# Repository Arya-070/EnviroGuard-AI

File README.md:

# 🚀 EnviroGuard-AI
### *A Smart, Modular Infrastructure Monitoring System Powered by Edge AI and ESP32-S3*

---

## 🌍 Overview
**EnviroGuard-AI** is a compact, modular, and powerful anomaly detection system built around the **ESP32-S3-WROOM-1** microcontroller. Designed specifically for smart infrastructure applications, this system brings together multiple environmental sensors, long-range wireless communication, and Edge AI capabilities.

With its **professionally designed 4-layer PCB**, onboard **LoRa (SX1262)**, **QSPI Flash** for TinyML models, and **I2S audio input**, it's ideal for detecting gas leaks, vibrations, fire hazards, and abnormal sounds in real-time. Its modular design makes it perfect for quick prototyping or field deployment.

---

## 🌟 Project Highlights
- 🛠️ Fully custom 4-layer **PCB designed in KiCad 7.0**
- 🔌 Powered via **USB-C** with onboard **CH340C USB-to-Serial** interface
- 💾 Includes **QSPI Flash** for storing Edge AI/TinyML models
- 🎤 Audio anomaly detection via **I2S MEMS microphone**
- 🌫️ Onboard sensors for gas, temperature, humidity, vibration, flame, and light
- 📡 Long-range communication using **SX1262 LoRa module**
- 🔋 Designed for **low-power, high-reliability** use cases
- 🧩 Modular expansion header for future hardware integrations

---

## 📌 GPIO Pinout & Connections

| GPIO Pin | Connected To         | Function / Role                    |
|----------|----------------------|------------------------------------|
| GPIO0    | SW_BOOT              | Boot mode selection                |
| GPIO1    | CH340C RXD           | UART TX                            |
| GPIO3    | CH340C TXD           | UART RX                            |
| GPIO10   | LED_STATUS           | Status LED                         |
| GPIO4    | MQ135_DATA           | Gas Sensor                         |
| GPIO5    | BH1750_SCL           | Light Sensor (I2C) Clock           |
| GPIO6    | EXP_IO1              | Expansion GPIO                     |
| GPIO12   | MPU6050_SDA          | I2C Data (Accelerometer)           |
| GPIO17   | MPU6050_SCL          | I2C Clock (Accelerometer)          |
| GPIO18   | FLAME_DO             | Flame Sensor Digital Out           |
| GPIO19   | MIC_CLK              | I2S Clock                          |
| GPIO20   | MIC_DATA             | I2S Data                           |
| GPIO21   | DHT22_DATA           | Temp & Humidity Sensor             |
| GPIO24   | LORA_BUSY            | LoRa Busy Pin                      |
| GPIO25   | LORA_MOSI            | SPI MOSI                           |
| GPIO26   | LORA_MISO            | SPI MISO                           |
| GPIO31   | LORA_NSS             | LoRa CS                            |
| GPIO32   | LORA_SCK             | SPI Clock                          |
| GPIO34   | LORA_IRQ0            | LoRa Interrupt                     |
| GPIO36   | LORA_RST             | LoRa Reset                         |
| GPIO35   | EXP_IO5              | Expansion GPIO                     |
| EN       | EN Switch            | Reset Circuit                      |

---

## 🧠 System Architecture

```mermaid
flowchart TD

    %% === Style Definitions ===
    classDef core fill:#ffe0f0,stroke:#d63384,stroke-width:1px,color:#000;
    classDef comm fill:#fff3cd,stroke:#ffc107,stroke-width:1px,color:#000;
    classDef sensor fill:#d1e7dd,stroke:#0f5132,stroke-width:1px,color:#000;
    classDef audio fill:#dbe4ff,stroke:#4c6ef5,stroke-width:1px,color:#000;
    classDef memory fill:#f8d7da,stroke:#842029,stroke-width:1px,color:#000;
    classDef power fill:#e2e3e5,stroke:#6c757d,stroke-width:1px,color:#000;
    classDef expansion fill:#e7f5ff,stroke:#228be6,stroke-width:1px,color:#000;

    %% === Main Power and MCU ===
    USB_C[USB-C Port]:::power --> Regulator[MP2333 Regulator]:::power
    Regulator --> ESP32S3[ESP32-S3 WROOM-1]:::core

    %% === Interfaces ===
    CH340C[CH340C USB-UART]:::comm --> ESP32S3

    %% === Peripherals ===
    ESP32S3 --> Flash[QSPI Flash Memory]:::memory
    ESP32S3 --> LoRa[SX1262 LoRa Module]:::comm
    ESP32S3 --> Audio[MEMS I2S Microphone]:::audio
    ESP32S3 --> Sensors[Sensor Hub]:::sensor
    ESP32S3 --> Expansion[Expansion IO Header]:::expansion

    %% === Sensors ===
    Sensors --> MQ135[MQ135 Gas Sensor]:::sensor
    Sensors --> MPU6050[MPU6050 Accelerometer]:::sensor
    Sensors --> Flame[Flame Sensor]:::sensor
    Sensors --> DHT22[DHT22 Temp & Humidity Sensor]:::sensor
    Sensors --> BH1750[BH1750 Light Sensor]:::sensor
```

---

## 🧩 Component Summary

| No. | Component              | Interface | Description                             |
|-----|------------------------|-----------|-----------------------------------------|
| 1   | ESP32-S3-WROOM-1       | -         | Main MCU with AI, BLE, WiFi             |
| 2   | SX1262 LoRa Module     | SPI       | Long-range wireless communication       |
| 3   | MEMS I2S Microphone    | I2S       | Captures audio for analysis             |
| 4   | MQ135                  | Analog    | Gas and air quality sensing             |
| 5   | MPU6050                | I2C       | Vibration/motion detection              |
| 6   | DHT22                  | Digital   | Temperature & Humidity                  |
| 7   | BH1750                 | I2C       | Ambient light measurement               |
| 8   | Flame Sensor (4-pin)   | Digital   | Detects flame or fire presence          |
| 9   | CH340C                 | UART      | USB-to-Serial for flashing and debug    |
| 10  | QSPI Flash (W25Q32JV)  | QSPI      | Stores ML models for inference          |
| 11  | USB-C Port             | Power     | Power and programming port              |
| 12  | MP2333 Regulator       | Power     | Converts 5V to 3.3V efficiently         |
| 13  | Expansion Header       | GPIO      | Breakout pins for add-ons and testing   |

---

## 📁 Folder Structure
```bash
EnviroGuard-AI/
│
├── README.md               
├── LICENSE                  
├── .gitignore               
│
├── EnviroGuard-AI_KiCAD_File/      
│   ├── EnviroGuard-AI.kicad_sch    
│   ├── EnviroGuard-AI.kicad_pcb    
│   ├── EnviroGuard-AI.pro          
│   ├── SCH_AUDIO_INPUT.kicad_sch    
│   ├── SCH_COMMUNICATION.kicad_sch  
│   ├── SCH_ENV_SENSORS.kicad_sch   
│   ├── SCH_EXPANSION.kicad_sch    
│   ├── SCH_MCU_CORE.kicad_sch      
│   ├── SCH_POWER_MANAGEMENT.kicad_sch 
│   ├── SCH_QSPI_STORAGE.kicad_sch   
│             
│
├── GERBER/                  
│   └── EnviroGuard-AI-Gerber.zip
│
IMAGES/    
│     ├── 3D_VIEW_1.png
│     ├── 3D_VIEW_2.png
│     ├── B.CU.png
│     ├── F.CU.png
│     ├── In1.CU.png
│     ├── In2.CU.png
│     ├── EDITOR_VIEW.png
│     ├── SCH_AUDIO_INPUT.png
│     ├── SCH_COMMUNICATION.png
│     ├── SCH_ENV_SENSORS.png
│     ├── SCH_EXPANSION.png
│     ├── SCH_MCU_CORE.png
│     ├── SCH_POWER_MANAGEMENT.png
│     ├── SCH_QSPI_STORAGE.png
│     ├── SCHEMATIC_ROOT.png
│     ├── SYSTEM_ARCHITECTURE.png
│     └── COMPONENTS_DOWNLOADED              
└── Backup_ZIP/             
    └── EnviroGuard-AI-backups/

```

---

## 🌱 Future Improvements
- Add a buzzer or RGB LED for better visual/audio alerts
- Enable deep sleep mode to save power during idle states
- Integrate a solar charging module (e.g., TP4056 or BQ24210)
- LoRaWAN gateway integration with cloud sync
- Run a trained ML model for local anomaly classification
- Add a companion web dashboard or mobile app

---

## 🌐 License
This project is released under the **MIT License**. You’re free to use, modify, and share it as you like.

---

## 🤝 Contributions & Feedback
- Found an issue? Open a GitHub issue.
- Have ideas or want to contribute? Pull requests are welcome.
- Collaborators in AI, IoT, or hardware design — feel free to connect!

---

**Let’s build a smarter, safer world with modular edge intelligence — one node at a time. ✨**

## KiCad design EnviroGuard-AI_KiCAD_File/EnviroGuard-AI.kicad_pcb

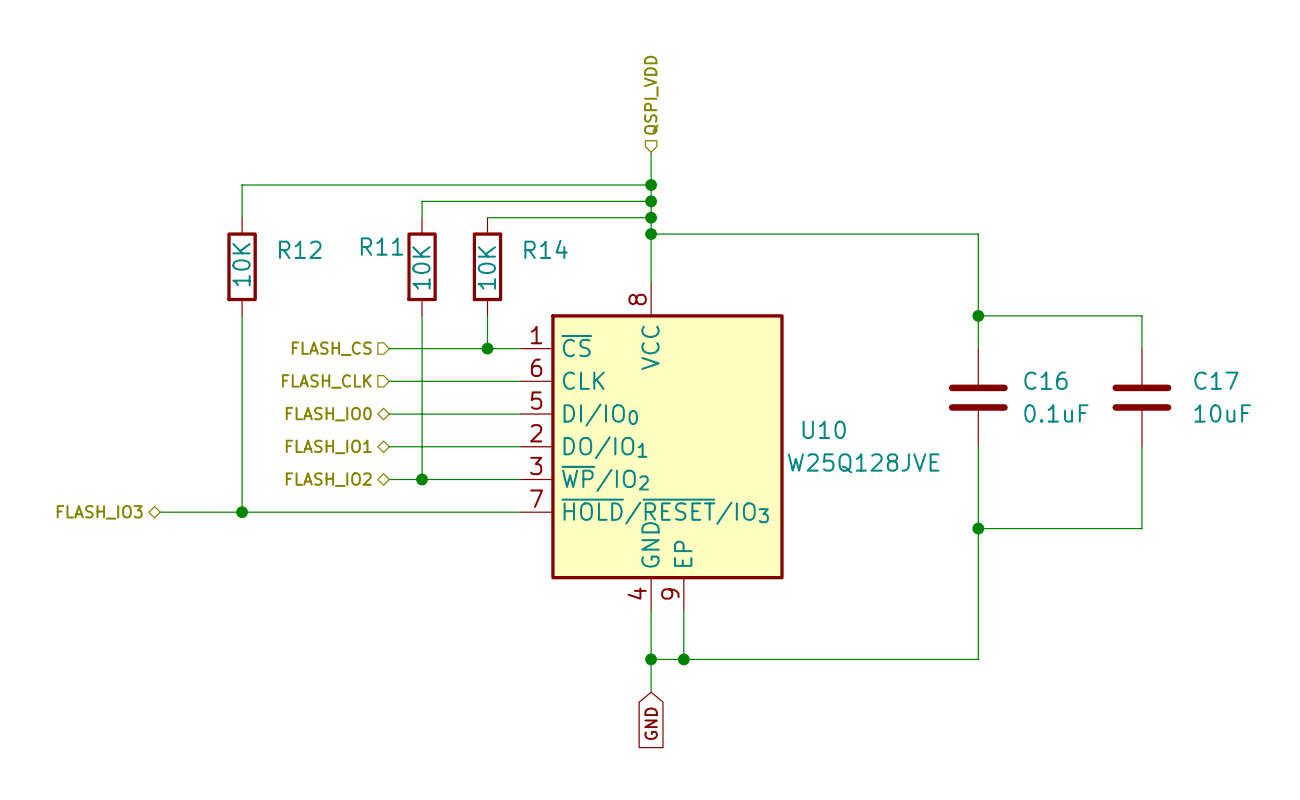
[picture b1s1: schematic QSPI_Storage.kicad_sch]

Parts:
C16: 0.1uF; C_0603_1608Metric
C17: 10uF; C_0603_1608Metric
R11, R12, R14: 10K; R_0603_1608Metric
U10: W25Q128JVE; WSON-8-1EP_8x6mm_P1.27mm_EP3.4x4.3mm

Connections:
/MCU_Core/+3V3: C16.1, C17.1, R11.1, R12.1, R14.1, U10.8 (VCC); also elsewhere on the board
/MCU_Core/FLASH_CLK: U10.6 (CLK); also elsewhere on the board
/MCU_Core/FLASH_CS: R14.2, U10.1 (~CS); also elsewhere on the board
/MCU_Core/FLASH_IO0: U10.5 (DI/IO_{0}); also elsewhere on the board
/MCU_Core/FLASH_IO1: U10.2 (DO/IO_{1}); also elsewhere on the board
/MCU_Core/FLASH_IO2: R11.2, U10.3 (~WP/IO_{2}); also elsewhere on the board
/MCU_Core/FL_1O3: R12.2, U10.7 (~HOLD/~RESET/IO_{3}); also elsewhere on the board
GND: C16.2, C17.2, U10.4 (GND), U10.9 (EP); also elsewhere on the board

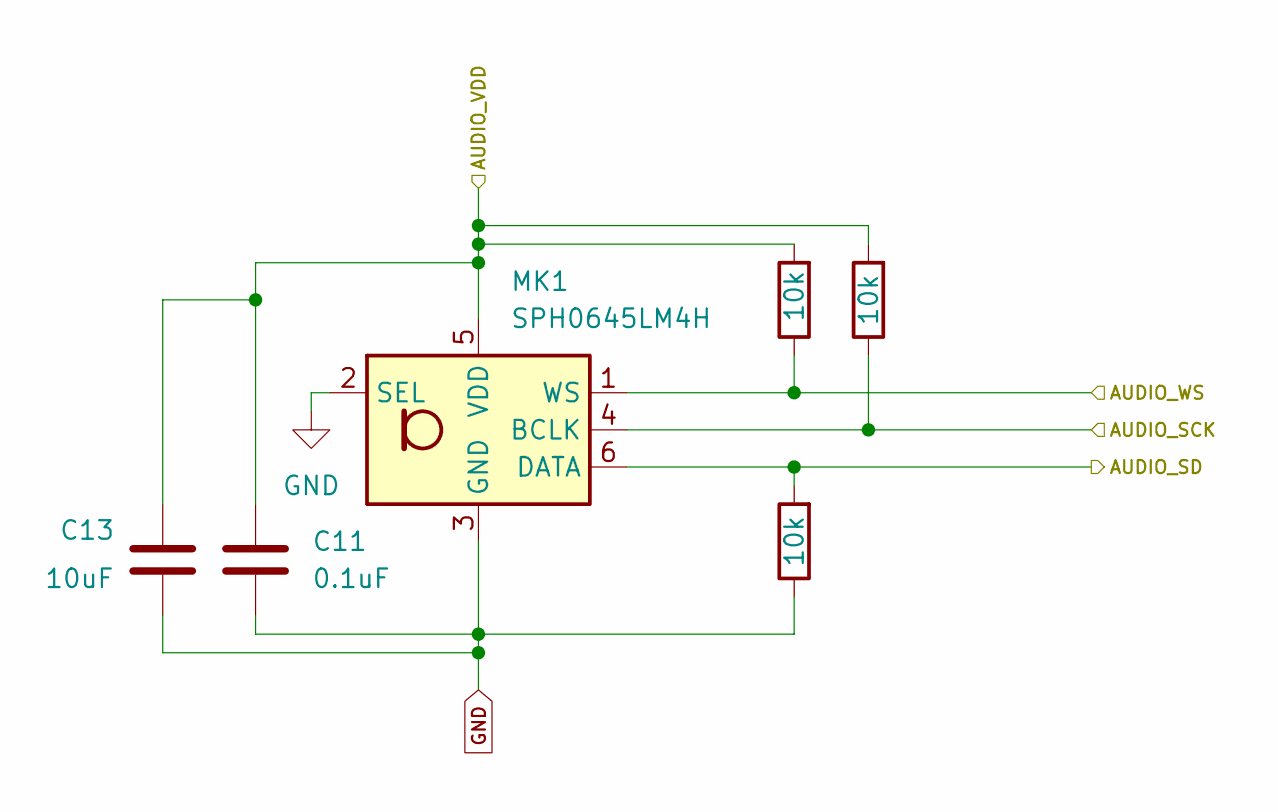
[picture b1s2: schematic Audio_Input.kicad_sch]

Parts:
C11: 0.1uF; C_0603_1608Metric
C13: 10uF; C_0603_1608Metric
MK1: SPH0645LM4H; Knowles_SPH0645LM4H-6_3.5x2.65mm
R5, R6, R7: 10k; R_0603_1608Metric

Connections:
/Audio_Input/AUDIO_SCK: MK1.4 (BCLK), R6.1; also elsewhere on the board
/Audio_Input/AUDIO_SD: MK1.6 (DATA), R7.2; also elsewhere on the board
/Audio_Input/AUDIO_WS: MK1.1 (WS), R5.1; also elsewhere on the board
/MCU_Core/+3V3: C11.1, C13.1, MK1.5 (VDD), R5.2, R6.2; also elsewhere on the board
GND: C11.2, C13.2, MK1.2 (SEL), MK1.3 (GND), R7.1; also elsewhere on the board

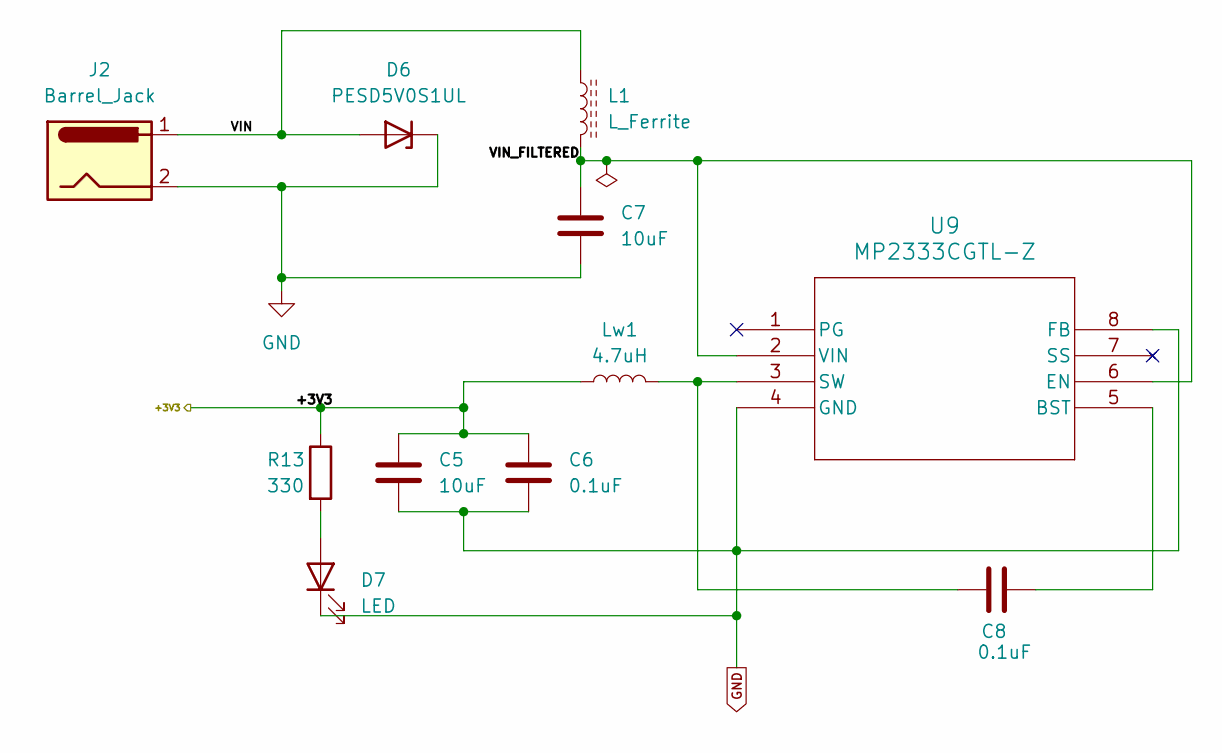
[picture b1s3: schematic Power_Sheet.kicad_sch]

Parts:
C5, C7: 10uF; C_0603_1608Metric
C6, C8: 0.1uF; C_0603_1608Metric
D6: PESD5V0S1UL; D_SOD-882
D7: LED; LED_0603_1608Metric
J2: Barrel_Jack; BarrelJack_Horizontal
L1: L_Ferrite; L_0603_1608Metric
Lw1: 4.7uH; L_1008_2520Metric
R13: 330; R_0603_1608Metric
U9: MP2333CGTL-Z; SOT583_MP2333C_MNP

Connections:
/MCU_Core/+3V3: C5.1, C6.1, Lw1.1, R13.1; also elsewhere on the board
/Power_Management/VIN: D6.2 (A), J2.1, L1.1
/Power_Management/VIN_FILTERED: C7.1, L1.2, U9.2 (VIN), U9.6 (EN)
GND: C5.2, C6.2, C7.2, D6.1 (K), D7.1 (K), J2.2, U9.4 (GND), U9.8 (FB); also elsewhere on the board
unnamed: D7.2 (A), R13.2
unnamed: C8.1, U9.5 (BST)
unnamed: C8.2, Lw1.2, U9.3 (SW)

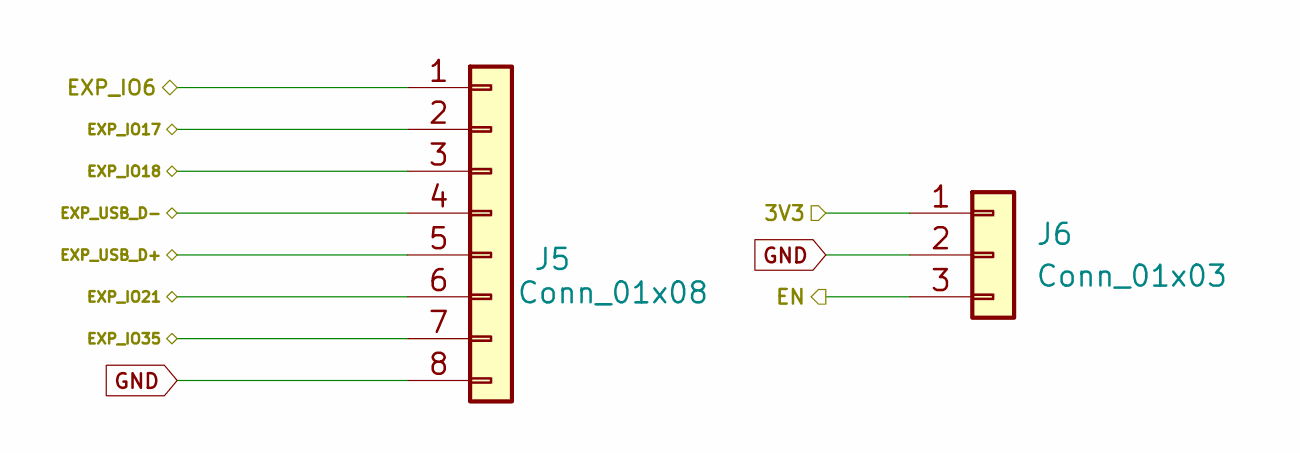
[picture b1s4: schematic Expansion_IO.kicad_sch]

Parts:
J5: Conn_01x08; PinSocket_1x08_P2.54mm_Vertical
J6: Conn_01x03; PinSocket_1x03_P2.54mm_Vertical

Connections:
/Expansion_IO/EXP_IO6: J5.1; also elsewhere on the board
/Expansion_IO/EXP_IO17: J5.2; also elsewhere on the board
/Expansion_IO/EXP_IO18: J5.3; also elsewhere on the board
/Expansion_IO/EXP_IO21: J5.6; also elsewhere on the board
/Expansion_IO/EXP_IO35: J5.7; also elsewhere on the board
/Expansion_IO/EXP_USB_D+: J5.5; also elsewhere on the board
/Expansion_IO/EXP_USB_D-: J5.4; also elsewhere on the board
/MCU_Core/+3V3: J6.1; also elsewhere on the board
/MCU_Core/EN: J6.3; also elsewhere on the board
GND: J5.8, J6.2; also elsewhere on the board

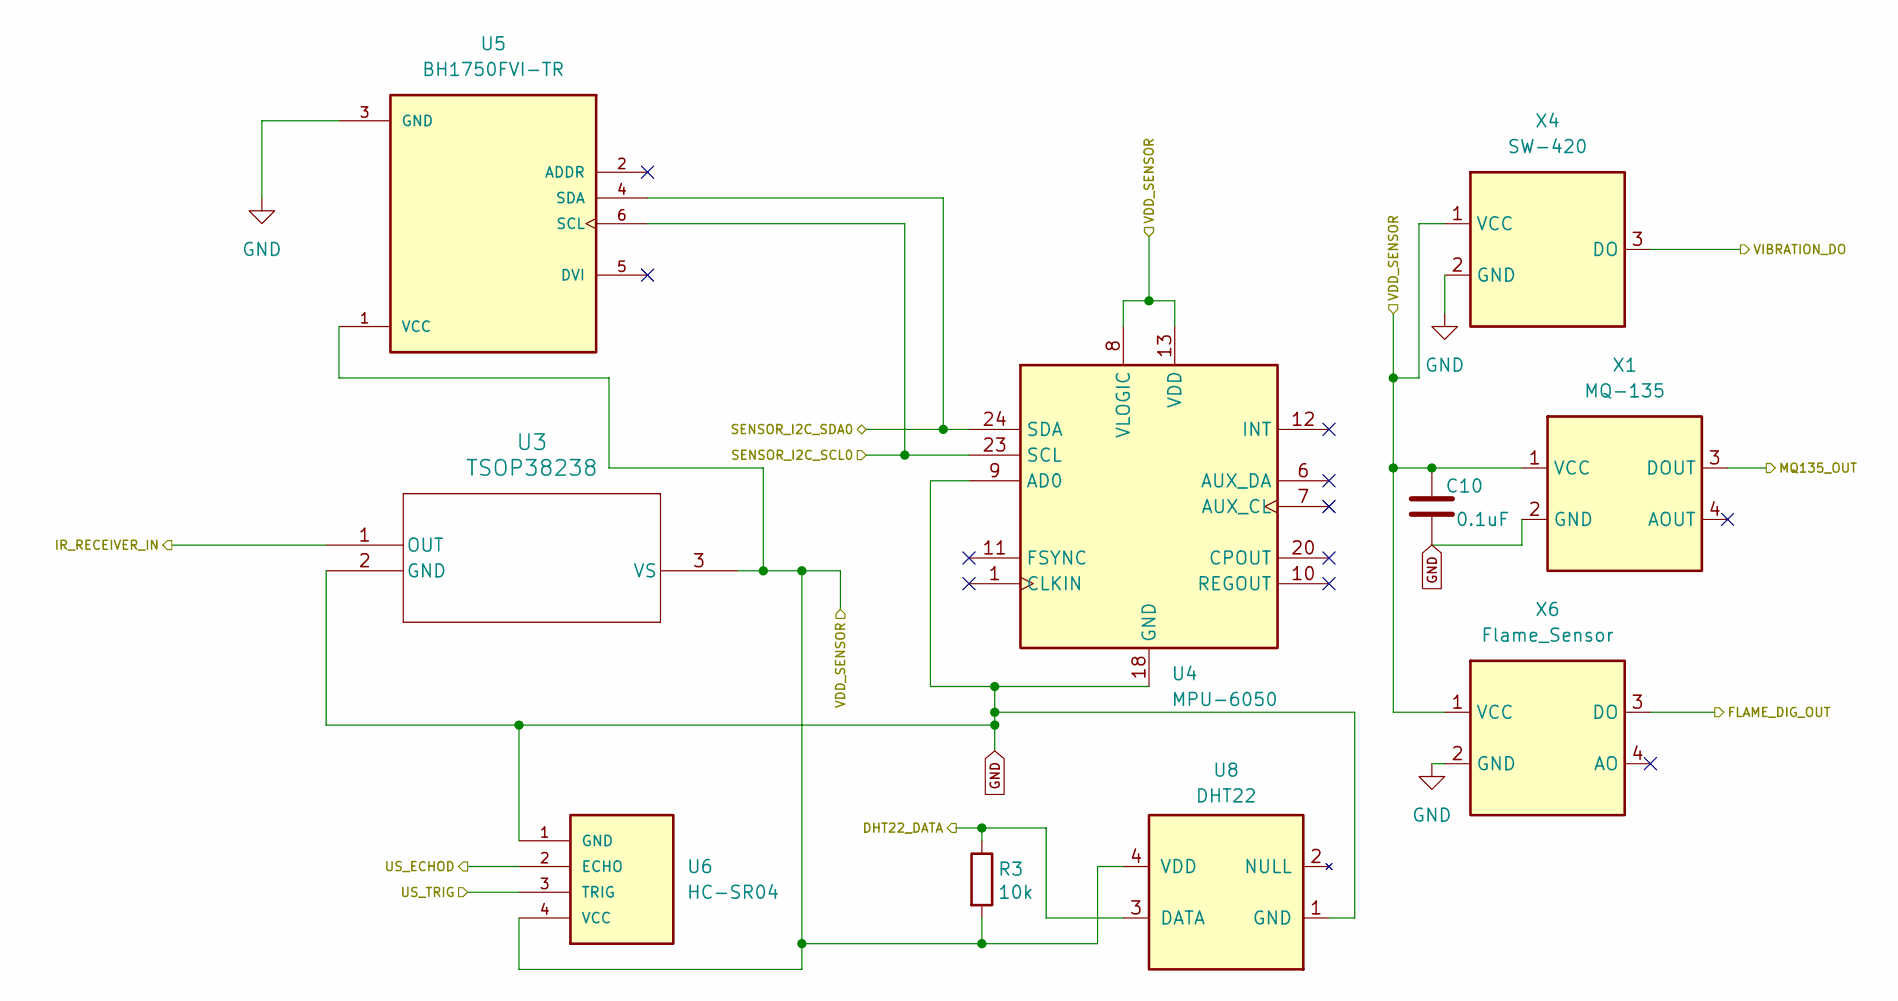
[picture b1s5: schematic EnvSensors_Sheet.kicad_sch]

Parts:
C10: 0.1uF; C_0603_1608Metric
R3: 10k; R_0603_1608Metric
U3: TSOP38238; TSOP382
U4: MPU-6050; InvenSense_QFN-24_4x4mm_P0.5mm
U5: BH1750FVI-TR; XDCR_BH1750FVI-TR; PARTREV D
U6: HC-SR04; JST_XH_S4B-XH-A_1x04_P2.50mm_Horizontal
U8: DHT22; JST_XH_S4B-XH-A_1x04_P2.50mm_Horizontal
X1: MQ-135; JST_XH_S4B-XH-A_1x04_P2.50mm_Horizontal
X4: SW-420; JST_XH_S3B-XH-A_1x03_P2.50mm_Horizontal
X6: Flame_Sensor; JST_XH_S4B-XH-A_1x04_P2.50mm_Horizontal

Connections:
/Environmental_Sensors/DHT22_DATA: R3.1, U8.3 (DATA); also elsewhere on the board
/Environmental_Sensors/FLAME_DIG_OUT: X6.3 (DO); also elsewhere on the board
/Environmental_Sensors/IR_RECEIVER_IN: U3.1 (OUT); also elsewhere on the board
/Environmental_Sensors/MQ135_OUT: X1.3 (DOUT); also elsewhere on the board
/Environmental_Sensors/SENSOR_I2C_SCL0: U4.23 (SCL), U5.6 (SCL); also elsewhere on the board
/Environmental_Sensors/SENSOR_I2C_SDA0: U4.24 (SDA), U5.4 (SDA); also elsewhere on the board
/Environmental_Sensors/US_ECHOD: U6.2 (ECHO); also elsewhere on the board
/Environmental_Sensors/US_TRIG: U6.3 (TRIG); also elsewhere on the board
/Environmental_Sensors/VIBRATION_DO: X4.3 (DO); also elsewhere on the board
/MCU_Core/+3V3: C10.1, R3.2, U3.3 (VS), U4.8 (VLOGIC), U4.13 (VDD), U5.1 (VCC), U6.4 (VCC), U8.4 (VDD), X1.1 (VCC), X4.1 (VCC), X6.1 (VCC); also elsewhere on the board
GND: C10.2, U3.2 (GND), U4.9 (AD0), U4.18 (GND), U5.3 (GND), U6.1 (GND), U8.1 (GND), X1.2 (GND), X4.2 (GND), X6.2 (GND); also elsewhere on the board

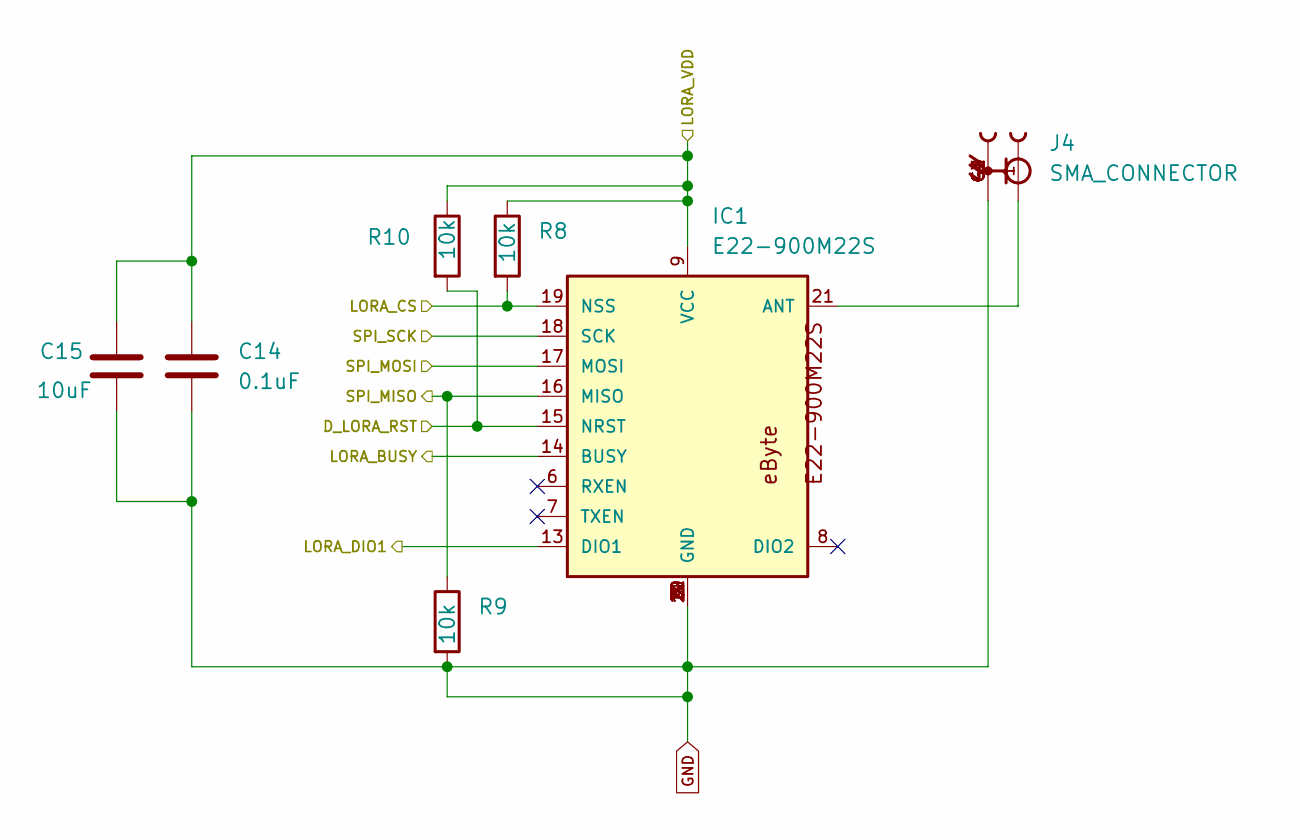
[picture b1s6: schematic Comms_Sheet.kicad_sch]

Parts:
C14: 0.1uF; C_0603_1608Metric
C15: 10uF; C_0603_1608Metric
IC1: E22-900M22S
J4: SMA_CONNECTOR; LPRS_SMA_CONNECTOR; PARTREV 1.3
R8, R9, R10: 10k; R_0603_1608Metric

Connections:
/Communication/D_LORA_RST: IC1.15 (NRST), R10.2; also elsewhere on the board
/Communication/LORA_BUSY: IC1.14 (BUSY); also elsewhere on the board
/Communication/LORA_CS: IC1.19 (NSS), R8.2; also elsewhere on the board
/Communication/LORA_DIO1: IC1.13 (DIO1); also elsewhere on the board
/Communication/SPI_MISO: IC1.16 (MISO), R9.1; also elsewhere on the board
/Communication/SPI_MOSI: IC1.17 (MOSI); also elsewhere on the board
/Communication/SPI_SCK: IC1.18 (SCK); also elsewhere on the board
/MCU_Core/+3V3: C14.1, C15.1, IC1.9 (VCC), R8.1, R10.1; also elsewhere on the board
GND: C14.2, C15.2, IC1.1 (GND), IC1.2 (GND), IC1.3 (GND), IC1.4 (GND), IC1.5 (GND), IC1.10 (GND), IC1.11 (GND), IC1.12 (GND), IC1.20 (GND), IC1.22 (GND), J4.G1, J4.G2, J4.G3, J4.G4, R9.2; also elsewhere on the board
unnamed: IC1.21 (ANT), J4.1

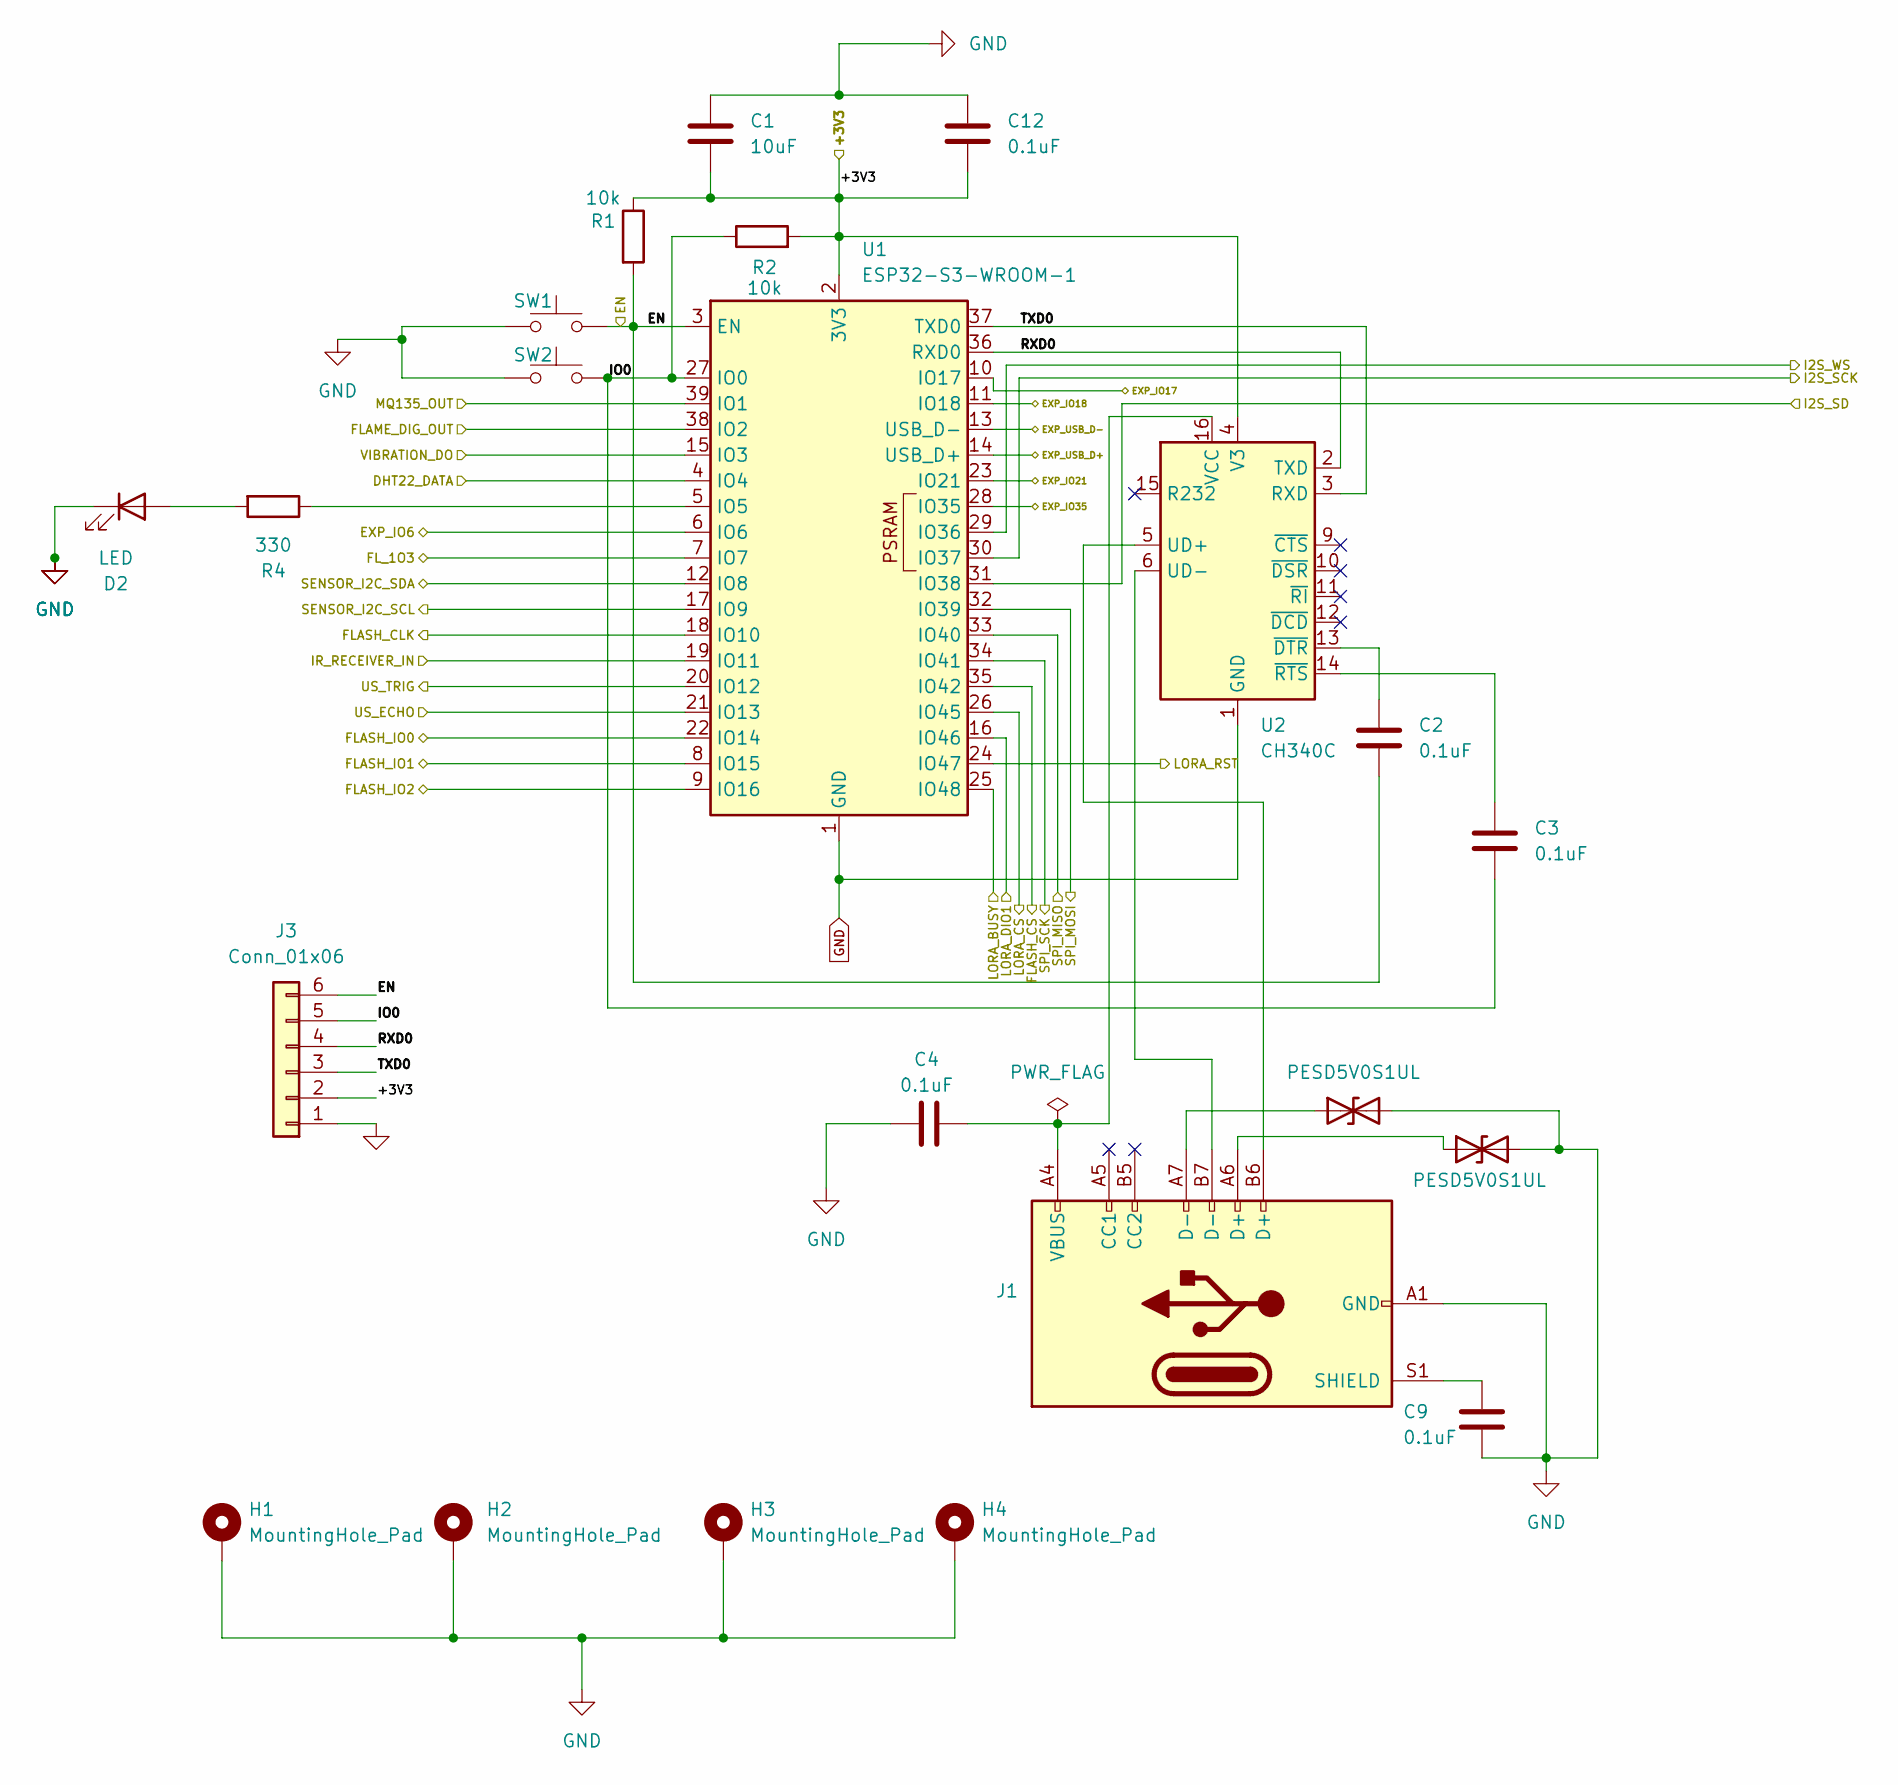
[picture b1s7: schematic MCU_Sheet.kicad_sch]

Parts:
C1: 10uF; C_0603_1608Metric
C2, C3, C4, C9, C12: 0.1uF; C_0603_1608Metric
D1, D3: PESD5V0S1UL; D_SOD-882
D2: LED; LED_0603_1608Metric
H1, H2, H3, H4: MountingHole_Pad; MountingHole_3.2mm_M3_Pad
J1: USB_C_Receptacle_USB2.0_14P; USB_C_Receptacle_HRO_TYPE-C-31-M-12
J3: Conn_01x06; PinHeader_1x06_P2.54mm_Vertical
R1, R2: 10k; R_0603_1608Metric
R4: 330; R_0603_1608Metric
SW1, SW2: SW_Push; SW_SPST_TL3342
U1: ESP32-S3-WROOM-1
U2: CH340C; SOIC-16_3.9x9.9mm_P1.27mm

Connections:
/Audio_Input/AUDIO_SCK: U1.30 (IO37); also elsewhere on the board
/Audio_Input/AUDIO_SD: U1.31 (IO38); also elsewhere on the board
/Audio_Input/AUDIO_WS: U1.29 (IO36); also elsewhere on the board
/Communication/D_LORA_RST: U1.24 (IO47); also elsewhere on the board
/Communication/LORA_BUSY: U1.25 (IO48); also elsewhere on the board
/Communication/LORA_CS: U1.26 (IO45); also elsewhere on the board
/Communication/LORA_DIO1: U1.16 (IO46); also elsewhere on the board
/Communication/SPI_MISO: U1.33 (IO40); also elsewhere on the board
/Communication/SPI_MOSI: U1.32 (IO39); also elsewhere on the board
/Communication/SPI_SCK: U1.34 (IO41); also elsewhere on the board
/Environmental_Sensors/DHT22_DATA: U1.4 (IO4); also elsewhere on the board
/Environmental_Sensors/FLAME_DIG_OUT: U1.38 (IO2); also elsewhere on the board
/Environmental_Sensors/IR_RECEIVER_IN: U1.19 (IO11); also elsewhere on the board
/Environmental_Sensors/MQ135_OUT: U1.39 (IO1); also elsewhere on the board
/Environmental_Sensors/SENSOR_I2C_SCL0: U1.17 (IO9); also elsewhere on the board
/Environmental_Sensors/SENSOR_I2C_SDA0: U1.12 (IO8); also elsewhere on the board
/Environmental_Sensors/US_ECHOD: U1.21 (IO13); also elsewhere on the board
/Environmental_Sensors/US_TRIG: U1.20 (IO12); also elsewhere on the board
/Environmental_Sensors/VIBRATION_DO: U1.15 (IO3); also elsewhere on the board
/Expansion_IO/EXP_IO6: U1.6 (IO6); also elsewhere on the board
/Expansion_IO/EXP_IO17: U1.10 (IO17); also elsewhere on the board
/Expansion_IO/EXP_IO18: U1.11 (IO18); also elsewhere on the board
/Expansion_IO/EXP_IO21: U1.23 (IO21); also elsewhere on the board
/Expansion_IO/EXP_IO35: U1.28 (IO35); also elsewhere on the board
/Expansion_IO/EXP_USB_D+: U1.14 (USB_D+); also elsewhere on the board
/Expansion_IO/EXP_USB_D-: U1.13 (USB_D-); also elsewhere on the board
/MCU_Core/+3V3: C1.2, C12.2, J3.2, R1.1, R2.2, U1.2 (3V3), U2.4 (V3); also elsewhere on the board
/MCU_Core/EN: C2.1, J3.6, R1.2, SW1.2, U1.3 (EN); also elsewhere on the board
/MCU_Core/FLASH_CLK: U1.18 (IO10); also elsewhere on the board
/MCU_Core/FLASH_CS: U1.35 (IO42); also elsewhere on the board
/MCU_Core/FLASH_IO0: U1.22 (IO14); also elsewhere on the board
/MCU_Core/FLASH_IO1: U1.8 (IO15); also elsewhere on the board
/MCU_Core/FLASH_IO2: U1.9 (IO16); also elsewhere on the board
/MCU_Core/FL_1O3: U1.7 (IO7); also elsewhere on the board
/MCU_Core/IO0: C3.1, J3.5, R2.1, SW2.2, U1.27 (IO0)
/MCU_Core/RXD0: J3.4, U1.36 (RXD0), U2.2 (TXD)
/MCU_Core/TXD0: J3.3, U1.37 (TXD0), U2.3 (RXD)
GND: C1.1, C4.1, C9.2, C12.1, D1.2 (A2), D2.1 (K), D3.2 (A2), H1.1, H2.1, H3.1, H4.1, J1.A1 (GND), J1.A12 (GND), J1.B1 (GND), J1.B12 (GND), J3.1, SW1.1, SW2.1, U1.1 (GND), U1.40 (GND), U1.41 (GND), U2.1 (GND); also elsewhere on the board
unnamed: D1.1 (A1), J1.A7 (D-)
unnamed: D2.2 (A), R4.2
unnamed: D3.1 (A1), J1.A6 (D+)
unnamed: C9.1, J1.S1 (SHIELD)
unnamed: R4.1, U1.5 (IO5)
unnamed: J1.B6 (D+), U2.5 (UD+)
unnamed: J1.B7 (D-), U2.6 (UD-)
unnamed: C4.2, J1.A4 (VBUS), J1.A9 (VBUS), J1.B4 (VBUS), J1.B9 (VBUS), U2.16 (VCC)
unnamed: C2.2, U2.13 (~DTR)
unnamed: C3.2, U2.14 (~RTS)

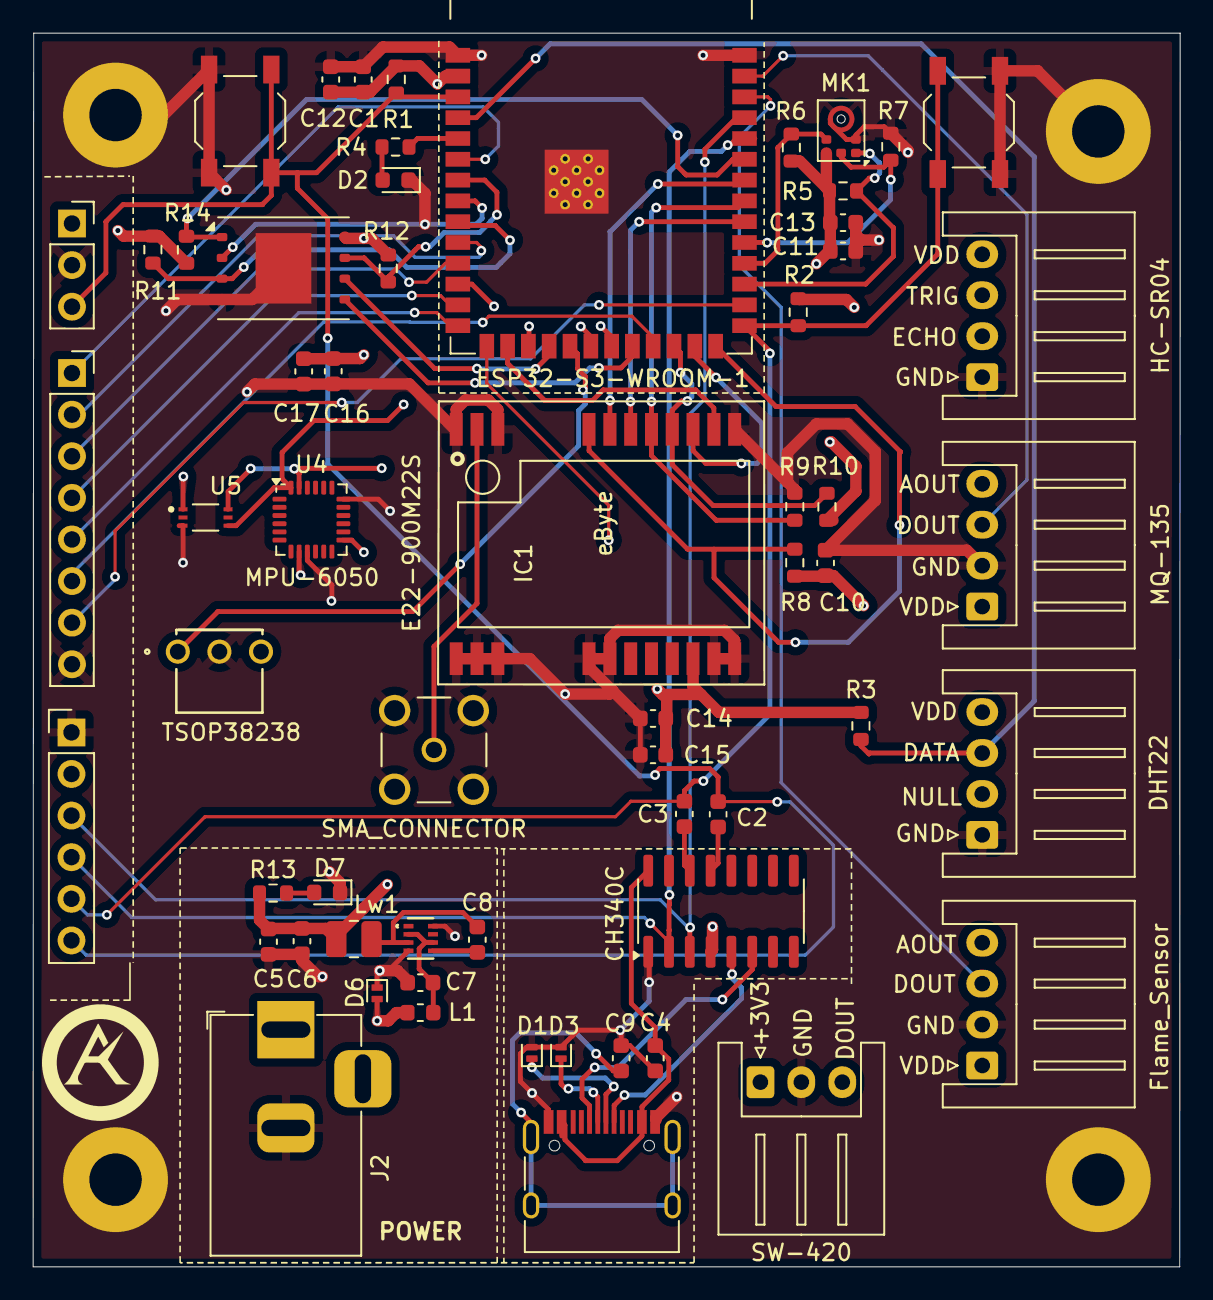
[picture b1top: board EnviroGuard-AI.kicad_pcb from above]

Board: 4 copper layers, 70.0 x 75.3 mm, 64 parts (0 on the bottom side), 54 nets.
